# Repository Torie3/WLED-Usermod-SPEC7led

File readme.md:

<p align="center">

  </p>

# Welcome to this wled Usermod ✨

This usermod enables connection of an ESP32C3 (you can build the firmware for other boards) to a flight controller , allowing users to select specific presets with a switch on their remote. Originally developed for Spec7 quads, this mod can be applied to any project where a preset needs to be activated based on a PWM signal received on a designated pin.

## ⚙️ How It Works
**WLED** is a project that allows easy control of addressable RGB lights. Our focus is on enabling users to switch between different presets set up in the WLED app using a physical switch on the controller. This is achieved by leveraging a built-in feature in **Betaflight or Inav** that generates a PWM (Pulse Width Modulation) signal on a specific pin—typically used for controlling servos. While we could have read data directly from the receiver, we opted for the PWM approach for several reasons outlined below.

### Advantages and Disadvantages of Using PWM
***Advantages:***
- **Compatible with Any Remote Protocol Supported by Betaflight:** Allows flexibility across various remote protocols.
- **Minimal Data Processing from Receiver:** Only the PWM signal is processed, improving the program’s speed and efficiency.
- **Standalone Use with PWM Receivers:** Can operate as a standalone unit with just the controller and LEDs, without a flight controller (FC).
- **Protocol Agnostic:** No need to adapt to specific protocols, making the setup easily adaptable.
- **Avoids UART Conflicts:** WLED may interfere with LED-receiver communication, particularly when multiple UARTs are used (one for the receiver and one for LEDs), as adding a software serial port can consume significant processing power.

***Disadvantages:***
- **Requires a Flight Controller or PWM Receiver:** Cannot function as a standalone unit with just the receiver, ESP, and LEDs.
- **Single-Channel Limitation:** Multiple channels for selecting presets would require additional wiring and pins on the FC.
- **Consumes a Pin on the Flight Controller:** Typically, the LED pin is used, but additional motor pins may also be viable.
### Advantages and Disadvantages of Direct Receiver Connection
***Advantages:***
- **Access to Full Receiver Data:** Allows use of multiple channels.
- **Standalone Operation:** Can function with just the receiver, ESP, and LEDs.
- **No Flight Controller Pin Usage:** Frees up all pins on the flight controller.

***Disadvantages:***
- **Requires Soldering on Receiver Pads:** Soldering two wires onto a single receiver pad can be cumbersome.
- **Limited to One Remote Protocol:** Only one remote protocol can be used in this configuration.
- **Increased Processing Power Demand:** Requires significant processing resources, potentially impacting performance.
### Conclusion
Considering these factors, we chose the PWM option, which offers a balanced approach in terms of flexibility, performance, and ease of setup. For instructions on setting up the system, refer to the Quick Start Guide.

## 💡 Quick Start Guide
**Betaflight Setup**
1) **Enable Servo on Flight Controller**

Ensure you flash your flight controller with servo enabled.

2) **Standard Flight Controller Setup**

Set up your flight controller as you normally would.

3) **Check Resource Pins in CLI**

Open the CLI and paste the following command to display all resources and their pin assignments:

`resource`

Find resource LED_STRIP 1 in the output and note the pin number next to it (e.g., A08).

4) **Reassign LED Strip Pin to Servo**

Enter the following commands in the CLI to remove the LED strip assignment from this pin and assign it to Servo 1:

```
resource LED_STRIP none
resource SERVO 1 "your noted pin number from step 4"
save
```

5) **Configure Servo Settings**

Go to the Servo tab and adjust the settings marked in the red box in the image below. Only the channel associated with the button to switch presets needs to be adjusted here. In the Receiver tab, you can check which button corresponds to which action. (We recommend using a 6-button switch on your controller; however, other setups may work, although results may vary.)

***Note: This configuration won’t work when connected to your computer unless “live mode” is enabled.***

### Hardware Setup
1) **Connect Ground**

Connect the ground on your flight controller to the ground on the ESP. This is mandatory, as it sets a shared reference.

2) **Connect Data Pin**

Connect the LED pin on your flight controller to gpio 2 on the ESP (make sure it's not pin 2, because on some boards they aren't the same). This wire carries the data.

3) **Power the ESP and LEDs**

Power the ESP as needed, and connect the LEDs like a standard WLED setup.

***Note: The following diagram provides an example for wiring. Do not copy it exactly; please research how to power your ESP safely. We are not liable for any physical or material damage.***

#### Custom PCB

***Warning: this pcb has not yet been tested, you can find all of the design files under the folder pcb. You should check the pcb design befor ordering.***

***If you want to order and test this pcb, we have added an excel file that includes all of the components. The components can be ordered from mouser and JLCPCB. Feel free to use other components.***

We recently introduced a custom PCB that integrates all the necessary components to run WLED on drones. This board includes a **5V@3A buck converter**, capable of stepping down **3s-6s voltage** to a stable **5V** supply.

The PCB measures **29mm × 21mm**, making it a perfect fit for a Spec7 quadcopter. Since only one side of the board is populated, you don’t need to worry about clearance on the mounting surface.

However, we highly recommend placing a **layer of electrical tape** beneath the PCB to prevent potential short circuits, as carbon fiber is conductive.

At its core, the board features an **ESP32-C3**, complete with all essential supporting components for power management and Wi-Fi transmission.

To simplify wiring, we've integrated a **logic level converter**, which shifts the **ESP32-C3's 3.3V signal** to **5V**, ensuring proper operation of LED strips. 

Additionally, we've included an extra GPIO pin, which can be used for:
- Receiving an input from the flight controller
- Connecting an additional LED strip

This extra GPIO is available as both a 3.3V pad and a 5V pad (via the logic level converter), allowing seamless integration with LED strips.

Below is the wiring diagram. Please note that your **flight controller may vary**, so be sure to check its specifications before wiring.

***Note: you should have a common ground between the PCB and flight controller to ensure proper operation of the PCB.***

### ESP Setup

This guide covers setup on Windows only. (Linux users should be able to manage on their own. Mac users: consider upgrading your hardware! Just kidding 😊)

1) **Download Firmware**

   - Navigate to `build_output/releases`, select the appropriate folder for your board, and download the `.bin` firmware file.
   - For ESP32 devices, download the bootloader file located in `.pio/build/your_board_here`.

2) **Set Up Programming Tool**

   - Follow the steps in [this guide](https://phoenixnap.com/kb/how-to-install-python-3-windows) to install Python. You may skip steps 4 and 7 as they are optional.
   - Once Python is installed, open Command Prompt (cmd) and run `pip install esptool` to install `esptool`.

3) **Connect ESP to Computer**

   - While holding the boot button on the ESP, plug it into your PC.
   - Open Device Manager and note the COM port your ESP is connected to.

4) **Upload Firmware**

***Note: These commands should be executed in the Command Prompt (cmd) on your Windows PC. You do not need to run it as an administrator.
If you're unsure how to open Command Prompt, click the Windows Start button, type `cmd`, and select the Command Prompt application. This will open a terminal where you can enter commands.***

   - First, install the bootloader:
     ```bash
     esptool -p com(your_com_port) -b 460800 write_flash 0x0 (path_to_bootloader_file)
     ```
     **Example**:
     ```bash
     esptool -p com13 -b 460800 write_flash 0x0 C:\Users\YourUser\Downloads\WLED-main\.pio\build\esp32c3dev\bootloader.bin
     ```
     - Once done, disconnect and reconnect the ESP while holding the boot button.

   - Now, upload the firmware:
     ```bash
     esptool -p com(your_com_port) -b 460800 write_flash 0x10000 (path_to_firmware_file)
     ```
     **Example**:
     ```bash
     esptool -p com13 -b 460800 write_flash 0x10000 C:\Users\YourUser\Downloads\WLED-main\build_output\release\WLED_0.14.4_ESP32-C3.bin
     ```
   - After completion, disconnect the ESP from your PC.

### Final Steps

Set up WLED as usual, ensuring you create six presets to avoid errors when switching. This setup is compatible with six-button switches (e.g., Radiomaster Boxer and TX16s). Future updates will include support for two- and three-position switches.

Enjoy your new LED setup on your Spec 7 quad!

*Disclaimer:*   

If you are prone to photosensitive epilepsy, we recommended you do **not** use this software.  
If you still want to try, don't use strobe, lighting or noise modes or high effect speed settings.

As per the MIT license, I assume no liability for any damage to you or any other person or equipment.

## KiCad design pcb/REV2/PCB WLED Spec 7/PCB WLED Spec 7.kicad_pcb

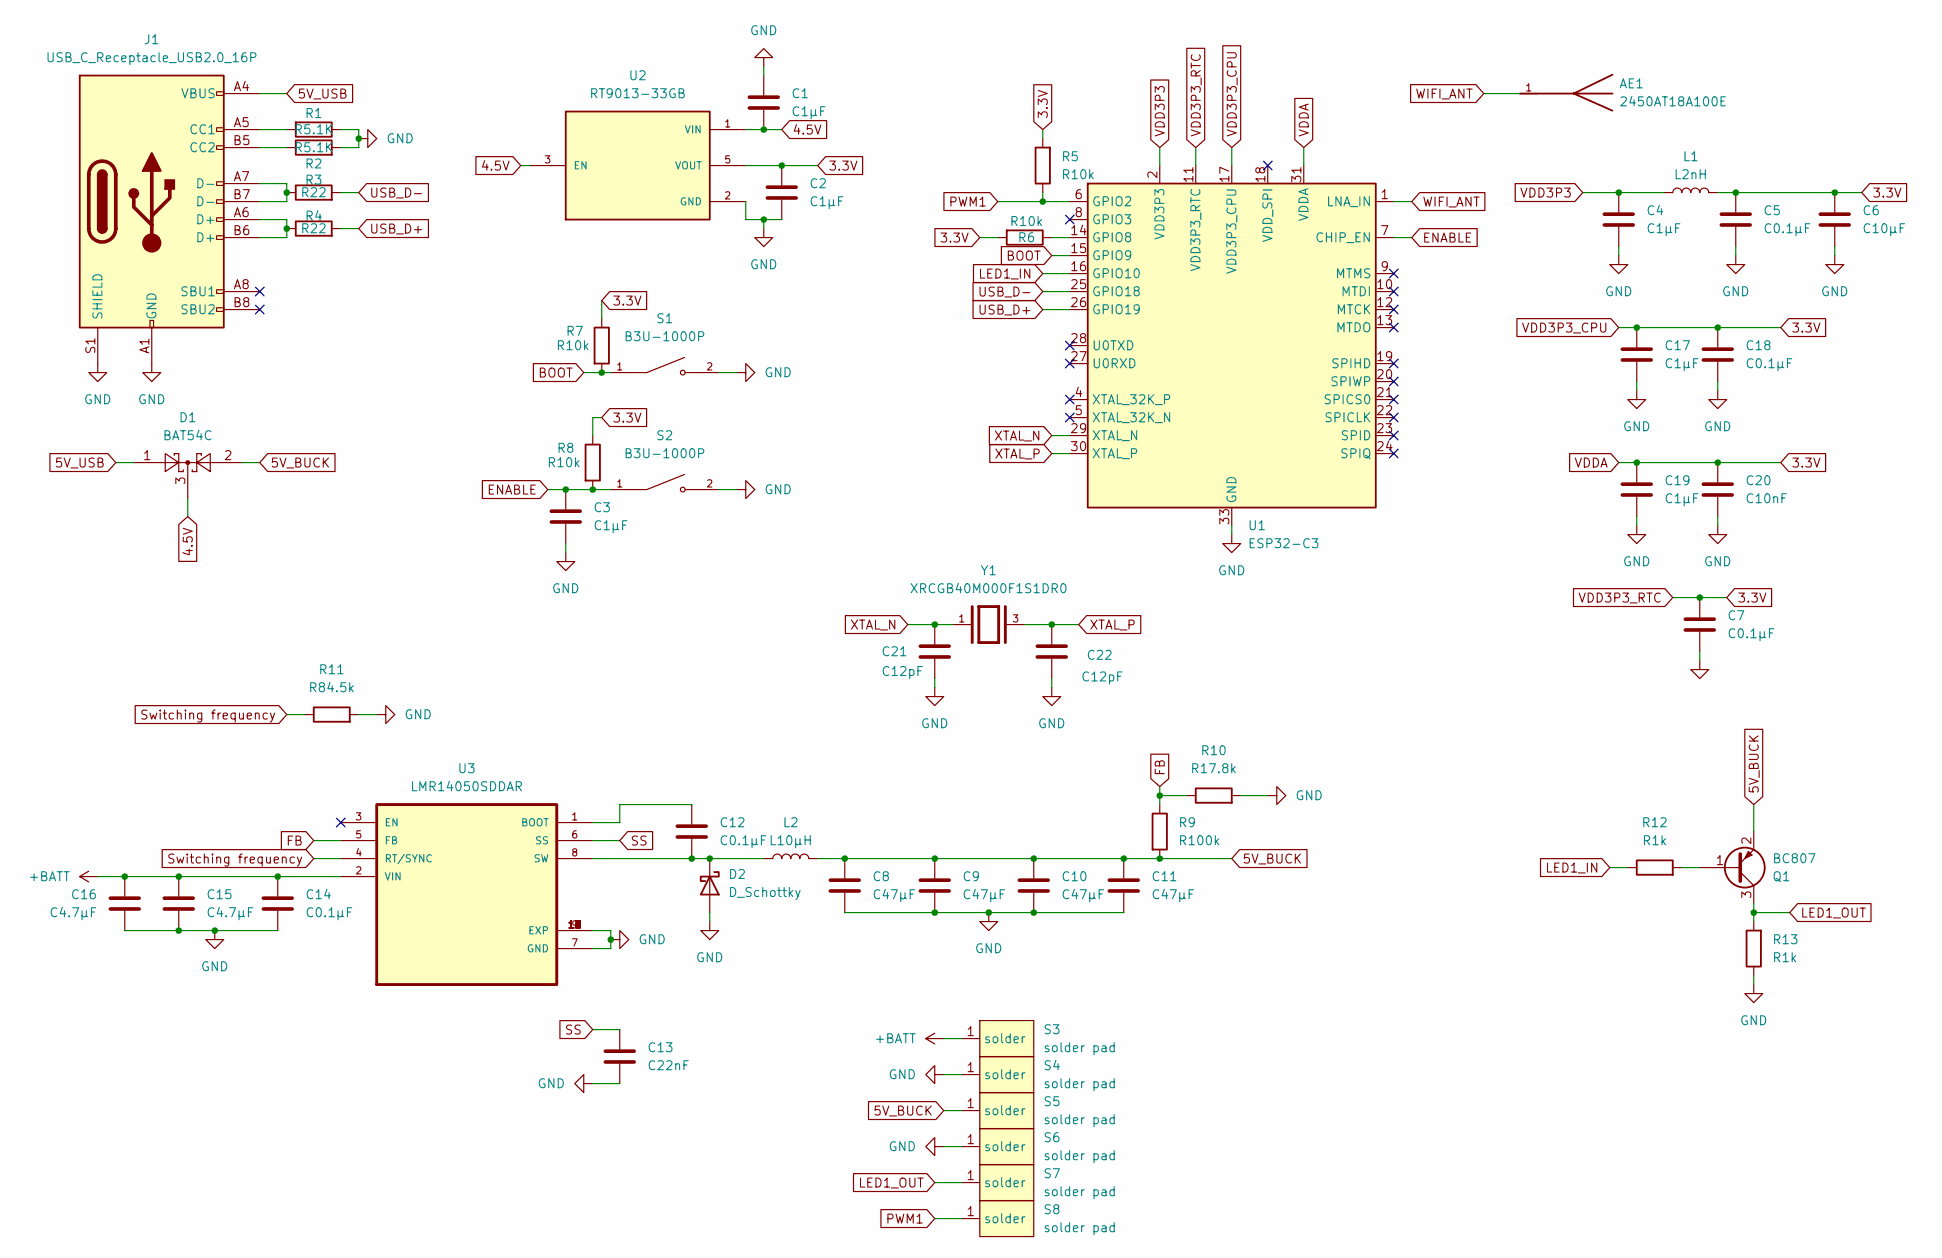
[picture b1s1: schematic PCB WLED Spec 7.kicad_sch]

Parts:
AE1: 2450AT18A100E; ANTC3216X140N; PARTREV 1.3
C1, C2, C3, C4, C17, C19: C1µF; C_0402_1005Metric
C5, C7, C12, C14, C18: C0.1µF; C_0402_1005Metric
C6: C10µF; C_0603_1608Metric
C8, C9, C10, C11: C47µF; C_1206_3216Metric
C13: C22nF; C_0402_1005Metric
C15, C16: C4.7µF; C_0805_2012Metric
C20: C10nF; C_0402_1005Metric
C21, C22: C12pF; C_0402_1005Metric
D1: BAT54C; SOT-23
D2: D_Schottky; DIOM6859X262N
J1: USB_C_Receptacle_USB2.0_16P; USB_C_Receptacle_JAE_DX07S016JA1R1500
L1: L2nH; L_0603_1608Metric
L2: L10µH; TECHFUSE SL1050-100M
Q1: BC807; SOT-23
R1, R2: R5.1K; R_0402_1005Metric
R3, R4: R22; R_0402_1005Metric_Pad0.72x0.64mm_HandSolder
R5, R6, R7, R8: R10k; R_0402_1005Metric
R9: R100k; R_0402_1005Metric
R10: R17.8k; R_0402_1005Metric
R11: R84.5k; R_0402_1005Metric
R12, R13: R1k; R_0402_1005Metric
S1, S2: B3U-1000P; SW_B3U-1000P
S3, S4, S5, S6, S7, S8: solder pad; solder pad small
U1: ESP32-C3; QFN-32-1EP_5x5mm_P0.5mm_EP3.7x3.7mm
U2: RT9013-33GB; SOT94P279X129-5N; PARTREV Aprill 2011
U3: LMR14050SDDAR; VREG_LM5017MR_NOPB
Y1: XRCGB40M000F1S1DR0; OSC_XRCGB40M000F1S1DR0; PARTREV N/A

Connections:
3.3V: C2.1, C5.1, C6.1, C7.1, C17.1, C18.1, C19.1, C20.1, L1.2, R5.2, R6.2, R7.1, R8.1, U1.11 (VDD3P3_RTC), U1.17 (VDD3P3_CPU), U1.31 (VDDA), U1.32 (VDDA), U2.5 (VOUT)
4.5V: C1.2, D1.3, U2.1 (VIN), U2.3 (EN)
5V_BUCK: C8.1, C9.1, C10.1, C11.1, D1.2, L2.2, Q1.2 (E), R9.2, S5.1 (solder)
5V_USB: D1.1, J1.A4 (VBUS), J1.A9 (VBUS), J1.B4 (VBUS), J1.B9 (VBUS)
+BATT: C14.1, C15.1, C16.1, S3.1 (solder), U3.2 (VIN)
BOOT: R7.2, S1.1, U1.15 (GPIO9)
ENABLE: C3.1, R8.2, S2.1, U1.7 (CHIP_EN)
FB: R9.1, R10.1, U3.5 (FB)
GND: C1.1, C2.2, C3.2, C4.2, C5.2, C6.2, C7.2, C8.2, C9.2, C10.2, C11.2, C13.2, C14.2, C15.2, C16.2, C17.2, C18.2, C19.2, C20.2, C21.2, C22.2, D2.2 (A), J1.A1 (GND), J1.A12 (GND), J1.B1 (GND), J1.B12 (GND), J1.S1 (SHIELD), R1.1, R2.2, R10.2, R11.2, R13.1, S1.2, S2.2, S4.1 (solder), S6.1 (solder), U1.33 (GND), U2.2 (GND), U3.7 (GND), U3.9 (EXP), U3.10 (EXP), U3.11 (EXP), U3.12 (EXP), U3.13 (EXP), U3.14 (EXP), U3.15 (EXP), U3.16 (EXP), U3.17 (EXP)
LED1_IN: R12.1, U1.16 (GPIO10)
LED1_OUT: Q1.3 (C), R13.2, S7.1 (solder)
unnamed: C12.2, D2.1 (K), L2.1, U3.8 (SW)
unnamed: J1.A5 (CC1), R1.2
unnamed: J1.B5 (CC2), R2.1
unnamed: J1.A6 (D+), J1.B6 (D+), R4.1
unnamed: J1.A7 (D-), J1.B7 (D-), R3.1
unnamed: Q1.1 (B), R12.2
unnamed: R6.1, U1.14 (GPIO8)
unnamed: C12.1, U3.1 (BOOT)
PWM1: R5.1, S8.1 (solder), U1.6 (GPIO2)
SS: C13.1, U3.6 (SS)
Switching frequency: R11.1, U3.4 (RT/SYNC)
USB_D+: R4.2, U1.26 (GPIO19)
USB_D-: R3.2, U1.25 (GPIO18)
VDD3P3: C4.1, L1.1, U1.2 (VDD3P3), U1.3 (VDD3P3)
WIFI_ANT: AE1.1, U1.1 (LNA_IN)
XTAL_N: C21.1, U1.29 (XTAL_N), Y1.1
XTAL_P: C22.1, U1.30 (XTAL_P), Y1.3

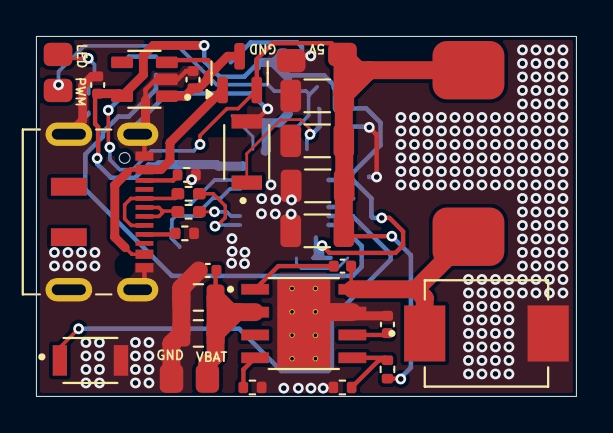
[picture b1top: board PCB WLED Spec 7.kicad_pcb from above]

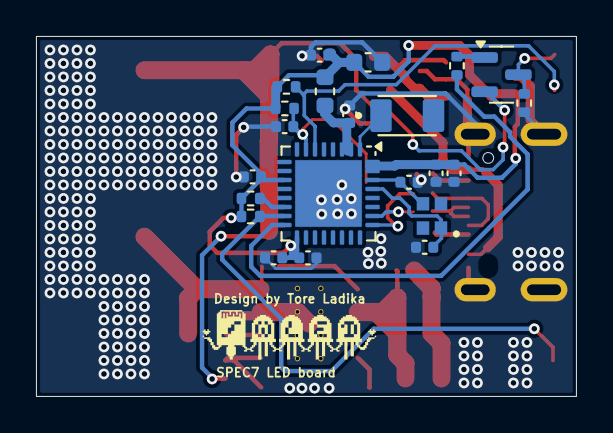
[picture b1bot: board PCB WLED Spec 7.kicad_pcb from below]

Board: 2 copper layers, 30.0 x 20.0 mm, 54 parts (22 on the bottom side), 28 nets.

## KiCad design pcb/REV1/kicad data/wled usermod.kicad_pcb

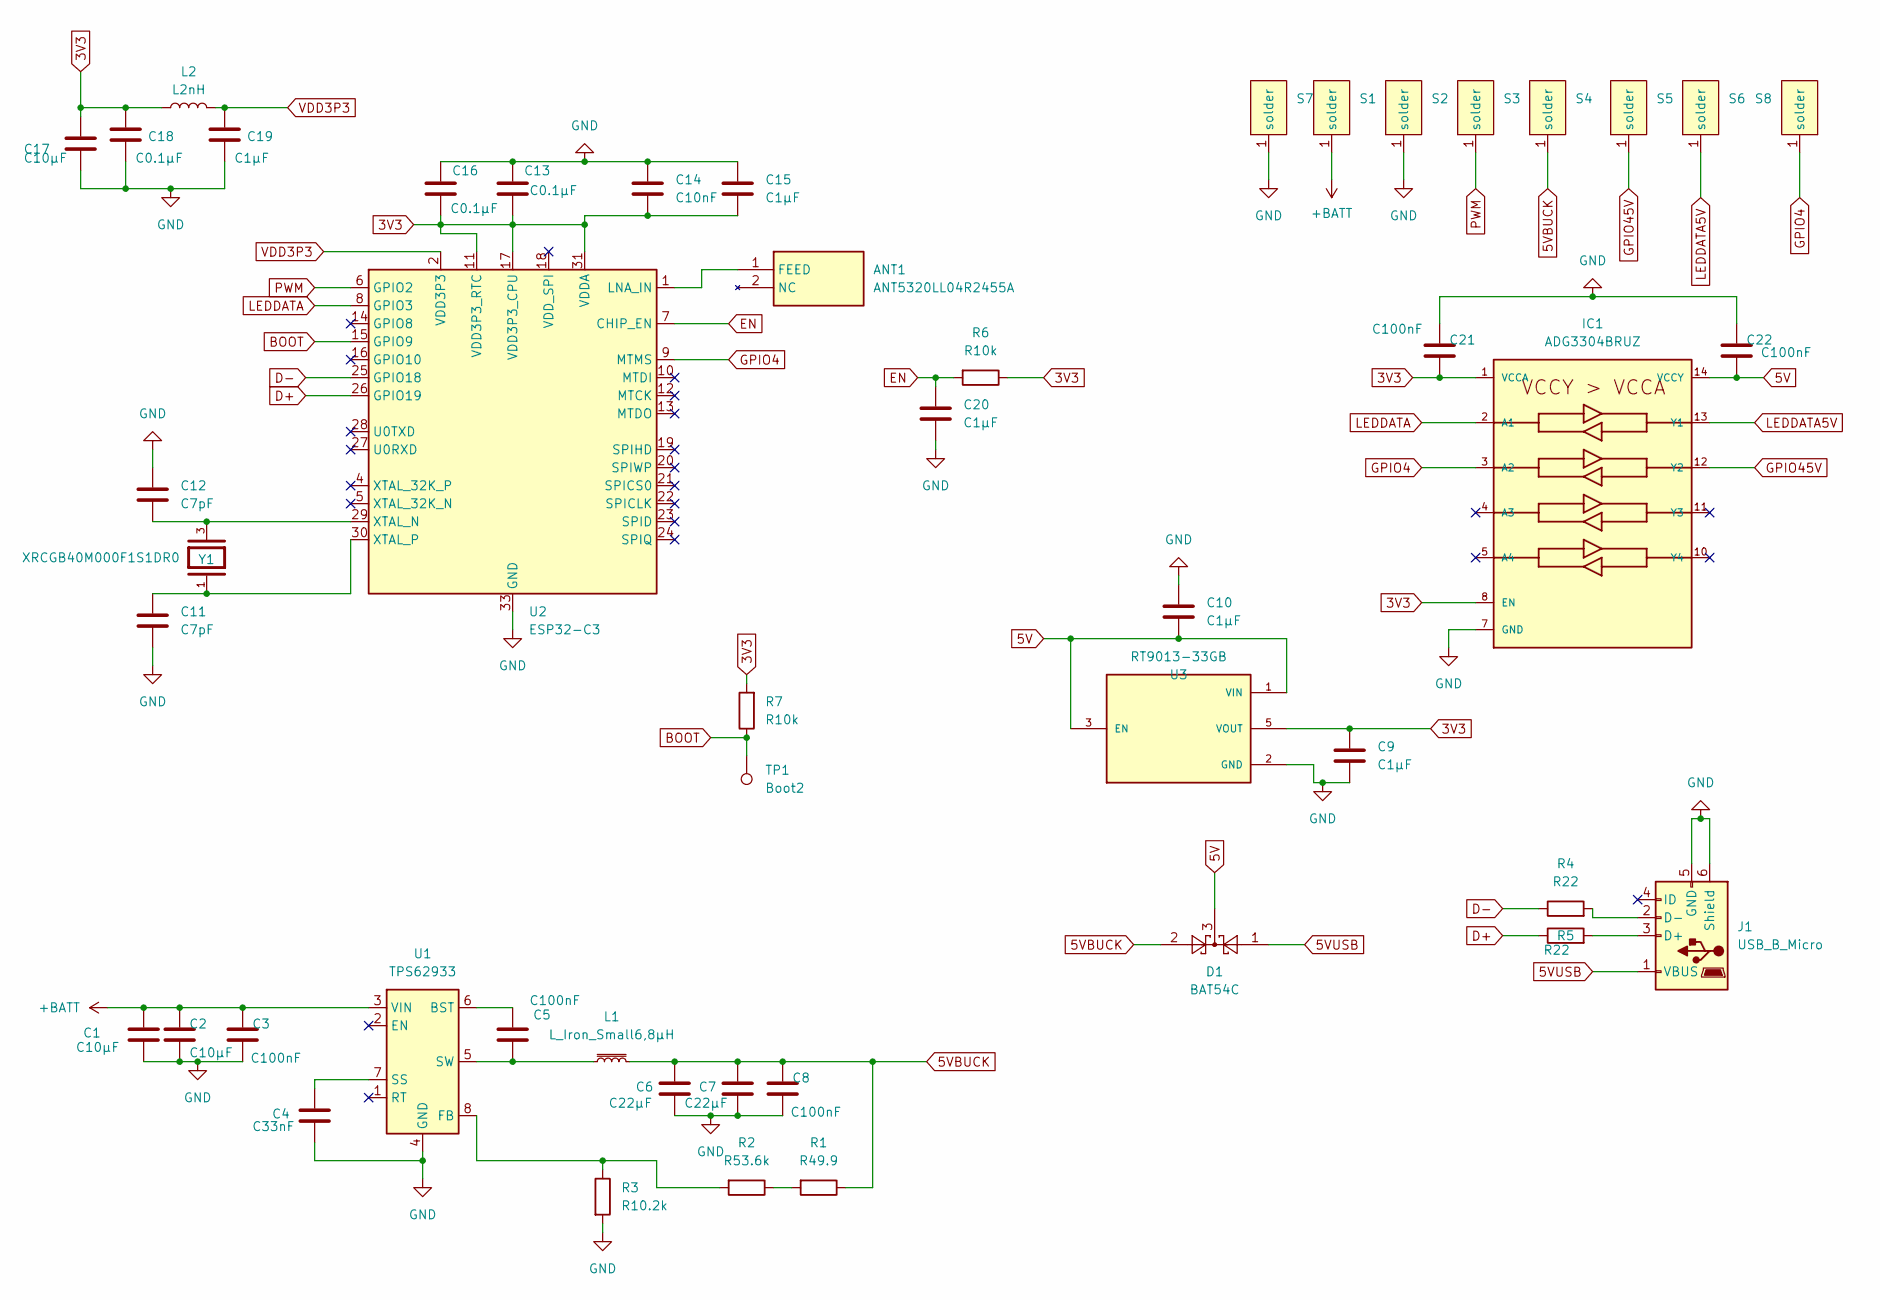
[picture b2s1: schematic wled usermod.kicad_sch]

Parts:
ANT1: ANT5320LL04R2455A; ANTC5320X170N; Manufacturer_Part_Number ANT5320LL04R2455A
C1, C2, C17: C10µF; C_0603_1608Metric_Pad1.08x0.95mm_HandSolder
C3, C5, C8, C21, C22: C100nF; C_0402_1005Metric_Pad0.74x0.62mm_HandSolder
C4: C33nF; C_1206_3216Metric_Pad1.33x1.80mm_HandSolder
C6, C7: C22µF; C_0603_1608Metric_Pad1.08x0.95mm_HandSolder
C9, C10, C15, C19, C20: C1µF; C_0402_1005Metric_Pad0.74x0.62mm_HandSolder
C11, C12: C7pF; C_0402_1005Metric_Pad0.74x0.62mm_HandSolder
C13, C16, C18: C0.1µF; C_0402_1005Metric_Pad0.74x0.62mm_HandSolder
C14: C10nF; C_0402_1005Metric_Pad0.74x0.62mm_HandSolder
D1: BAT54C; SOT-23
IC1: ADG3304BRUZ; TSSOP14
J1: USB_B_Micro; USB_Micro-B_Amphenol_10118194_Horizontal
L1: L_Iron_Small6,8µH; 7443734948068 inductor
L2: L2nH; L_0402_1005Metric_Pad0.77x0.64mm_HandSolder
R1: R49.9; R_0402_1005Metric_Pad0.72x0.64mm_HandSolder
R2: R53.6k; R_0603_1608Metric_Pad0.98x0.95mm_HandSolder
R3: R10.2k; R_0603_1608Metric_Pad0.98x0.95mm_HandSolder
R4, R5: R22; R_0402_1005Metric_Pad0.72x0.64mm_HandSolder
R6: R10k; R_0402_1005Metric_Pad0.72x0.64mm_HandSolder
R7: R10k; R_0402_1005Metric
S1, S2, S3, S4, S5, S6, S7, S8: solder pad; solder pad small
TP1: Boot2; TestPoint_Pad_D1.0mm
U1: TPS62933; SOT-583-8
U2: ESP32-C3; QFN-32-1EP_5x5mm_P0.5mm_EP3.7x3.7mm
U3: RT9013-33GB; SOT94P279X129-5N; PARTREV Aprill 2011
Y1: XRCGB40M000F1S1DR0; OSC_XRCGB40M000F1S1DR0; PARTREV N/A

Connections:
3V3: C9.1, C13.2, C14.2, C15.2, C16.2, C17.1, C18.1, C21.2, IC1.1 (VCCA), IC1.8 (EN), L2.1, R6.1, R7.2, U2.11 (VDD3P3_RTC), U2.17 (VDD3P3_CPU), U2.31 (VDDA), U2.32 (VDDA), U3.5 (VOUT)
5V: C10.2, C22.2, D1.3, IC1.14 (VCCY), U3.1 (VIN), U3.3 (EN)
5VBUCK: C6.1, C7.1, C8.1, D1.2, L1.2, R1.1, S4.1 (solder)
5VUSB: D1.1, J1.1 (VBUS)
+BATT: C1.1, C2.1, C3.1, S1.1 (solder), U1.3 (VIN)
BOOT: R7.1, TP1.1, U2.15 (GPIO9)
D+: R5.1, U2.26 (GPIO19)
D-: R4.1, U2.25 (GPIO18)
EN: C20.1, R6.2, U2.7 (CHIP_EN)
GND: C1.2, C2.2, C3.2, C4.2, C6.2, C7.2, C8.2, C9.2, C10.1, C11.1, C12.2, C13.1, C14.1, C15.1, C16.1, C17.2, C18.2, C19.2, C20.2, C21.1, C22.1, IC1.7 (GND), J1.5 (GND), J1.6 (Shield), R3.2, S2.1 (solder), S7.1 (solder), U1.4 (GND), U2.33 (GND), U3.2 (GND)
GPIO4: IC1.3 (A2), S8.1 (solder), U2.9 (MTMS)
GPIO45V: IC1.12 (Y2), S5.1 (solder)
LEDDATA: IC1.2 (A1), U2.8 (GPIO3)
LEDDATA5V: IC1.13 (Y1), S6.1 (solder)
unnamed: ANT1.1 (FEED), U2.1 (LNA_IN)
unnamed: J1.3 (D+), R5.2
unnamed: J1.2 (D-), R4.2
unnamed: R1.2, R2.1
unnamed: C5.1, U1.6 (BST)
unnamed: R2.2, R3.1, U1.8 (FB)
unnamed: C4.1, U1.7 (SS)
unnamed: C5.2, L1.1, U1.5 (SW)
unnamed: C12.1, U2.29 (XTAL_N), Y1.3
unnamed: C11.2, U2.30 (XTAL_P), Y1.1
PWM: S3.1 (solder), U2.6 (GPIO2)
VDD3P3: C19.1, L2.2, U2.2 (VDD3P3), U2.3 (VDD3P3)

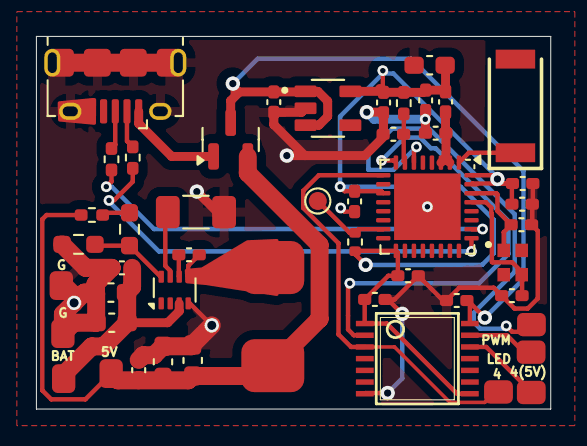
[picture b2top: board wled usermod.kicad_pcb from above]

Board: 2 copper layers, 28.6 x 20.7 mm, 48 parts (0 on the bottom side), 26 nets.

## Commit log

2024-10-25 PWM instead of CRSF
2024-10-25 fixed interupts bug
2024-10-26 6 position switch used
2024-10-27 esp32c3
2024-10-28 Picture added
2024-10-28 esp32c3 devboard change and build
2024-11-01 debug enabled
2024-11-06 delete
2024-11-06 updated everything
    -delete platformoverried
    -to v1 usermod
    - esp32c3 build
2024-11-06 add images
2024-11-06 add missing folders
2024-11-18 Update usermod.cpp
    6*if => for loop
2024-11-18 pcb schematic basic
2024-11-21 folder made called pcb
2024-11-21 update schematic for pcb
2024-11-21 update logboek
2025-01-20 pcb uploaden
2025-02-20 add pcb design files
2025-02-20 add images
    wiring diagram and pcb images
2025-03-13 Add list of components.
2025-09-02 update logboek
    nieuw schooljaar
2025-09-02 add rev2 of pcb
2025-09-05 eddited pcb rev2 and logboek update
2025-09-09 update pcb rev 2
2025-09-12 pcb rev2 update
2025-09-16 pcb v2 update
2025-09-23 pcb layout finished
2025-09-30 pcb routing done
2025-10-07 pcb afgewerkt
2025-10-10 pcb finished or I hope so
2025-10-24 logboek update
